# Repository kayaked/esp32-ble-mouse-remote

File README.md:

## Bluetooth LE Mouse Remote

Bluetooth LE hybrid of a computer mouse and TV remote. (software/electronics)

Software written in C using ESP-IDF and ESP32-based PCB designed in KiCad 7.

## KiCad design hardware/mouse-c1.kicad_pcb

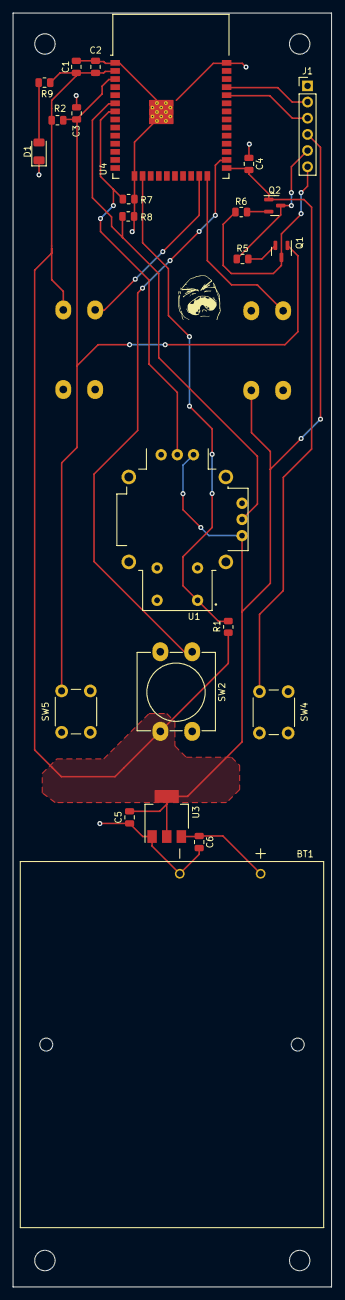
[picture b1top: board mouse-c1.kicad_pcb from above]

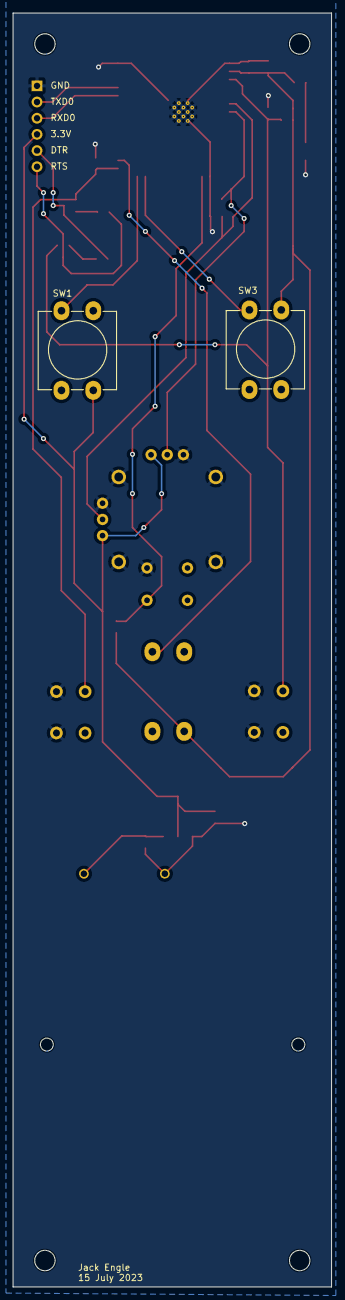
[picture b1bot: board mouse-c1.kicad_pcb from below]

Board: 2 copper layers, 50.0 x 200.0 mm, 30 parts (2 on the bottom side), 17 nets.

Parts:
BT1: Battery; BAT_BA3AAPC-UL94V-0
C1, C3, C4: 0.1uF; C_0805_2012Metric
C2: 22uF; C_0805_2012Metric
C5: 100uF; C_0805_2012Metric
C6: 10uF; C_0805_2012Metric
D1: LED; LED_1206_3216Metric
H1, H2, H3, H4: MountingHole; MountingHole_3.2mm_M3
J1: Conn_01x06; PinHeader_1x06_P2.54mm_Vertical
Q1, Q2: NPN; SOT-23
R1: 2.2kΩ; R_0805_2012Metric
R2, R5, R6, R7, R8: 10kΩ; R_0805_2012Metric
R9: 220Ω; R_0805_2012Metric
SW1, SW2, SW3: SW_Push; SW_PUSH-12mm_Wuerth-430476085716
SW4, SW5: SW_Push; SW_PUSH_6mm
U1: COM-09032; XDCR_COM-09032
U3: LM1117MP-3.3; SOT-223-3_TabPin2
U4: ESP32-WROOM-32D

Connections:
+3.3V: C1.1, C2.1, C5.1, J1.4, R1.1, R2.1, R9.1, SW1.2, SW2.2, SW3.2, U1.H1 (H+), U1.V1 (V+), U3.2 (VO), U4.2 (VDD)
+BATT: C6.1, U3.3 (VI)
/DTR: J1.5, Q2.3 (E), R5.1
/EN: C3.1, Q1.1 (C), R2.2, SW5.1, U4.3 (EN)
/IO0: C4.2, Q2.1 (C), SW4.1, U4.25 (IO0)
/RTS: J1.6, Q1.3 (E), R6.1
GND: C1.2, C2.2, C3.2, C4.1, C5.2, C6.2, D1.1 (K), J1.1, R7.2, R8.2, SW4.2, SW5.2, U1.B2A (SEL-), U1.H3 (H-), U1.S1 (SHIELD), U1.S2 (SHIELD), U1.S3 (SHIELD), U1.S4 (SHIELD), U1.V3 (V-), U3.1 (GND), U4.1 (GND), U4.15 (GND), U4.38 (GND), U4.39 (GND)
unnamed: D1.2 (A), R9.2
unnamed: J1.2, U4.35 (TXD0/IO1)
unnamed: J1.3, U4.34 (RXD0/IO3)
unnamed: Q1.2 (B), R5.2
unnamed: Q2.2 (B), R6.2
unnamed: R7.1, U1.H2 (H), U4.7 (IO35)
unnamed: R8.1, U1.V2 (V), U4.6 (IO34)
unnamed: SW1.1, U4.24 (IO2)
unnamed: SW2.1, U4.26 (IO4)
unnamed: SW3.1, U4.23 (IO15)

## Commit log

2023-07-22 Hardware Rev1 KiCad
    Schematic, PCB and Project file made in KiCad
2023-07-23 Initial Software Commit (Rewrite)
    SW/FW barebones mouse demo. Legacy software used BT ESP_HID_DEVICE, new version uses BLE_HID_DEVICE_DEMO
2023-07-23 ADC Setup, UUID, Clock
2023-07-23 Electrical Schematic/PCB Images (PNG)
2023-07-25 Implemented GPIO/isr/task
2023-07-25 State 1 w/ volume control
2023-07-26 Remote Mode controls
    Further code commits will be minor fixes
2023-07-26 removed demo task
